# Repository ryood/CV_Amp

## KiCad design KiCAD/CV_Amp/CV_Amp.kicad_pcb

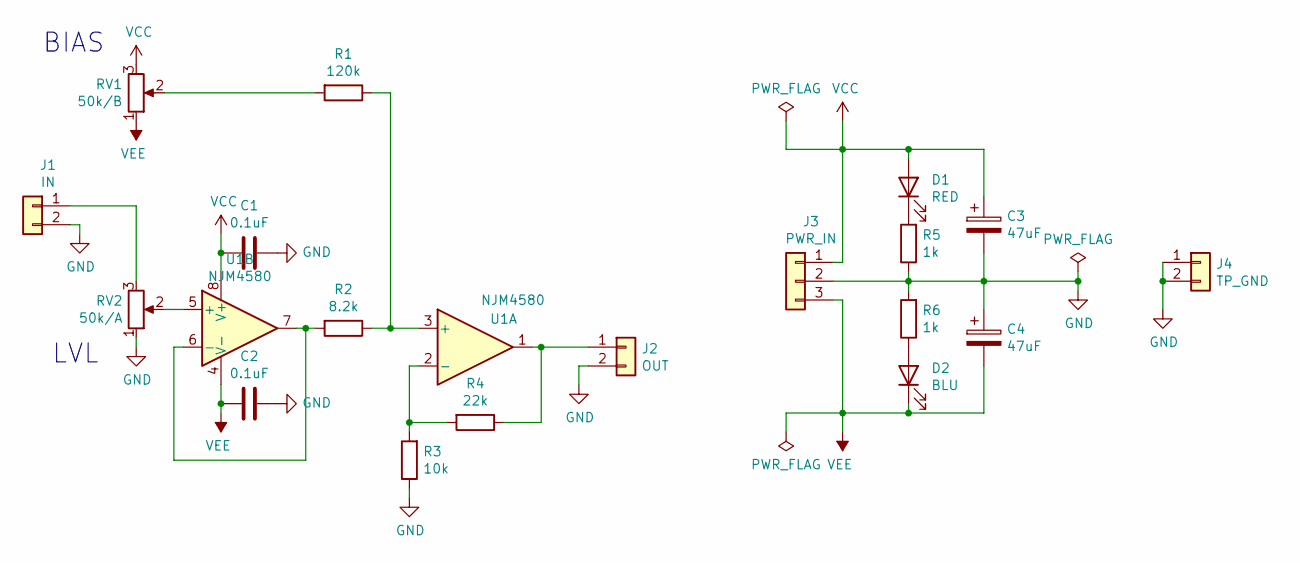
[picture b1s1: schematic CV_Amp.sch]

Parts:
C1, C2: 0.1uF; C_Disc_D3.0mm_W1.6mm_P2.50mm
C3, C4: 47uF; CP_Radial_D6.3mm_P2.50mm
D1: RED; LED_D3.0mm
D2: BLU; LED_D3.0mm
J1: IN; JST_XH_B2B-XH-A_1x02_P2.50mm_Vertical
J2: OUT; JST_XH_B2B-XH-A_1x02_P2.50mm_Vertical
J3: PWR_IN; JST_XH_B3B-XH-A_1x03_P2.50mm_Vertical
J4: TP_GND; PinHeader_1x02_P2.54mm_Vertical
R1: 120k; R_Axial_DIN0207_L6.3mm_D2.5mm_P7.62mm_Horizontal
R2: 8.2k; R_Axial_DIN0207_L6.3mm_D2.5mm_P7.62mm_Horizontal
R3: 10k; R_Axial_DIN0207_L6.3mm_D2.5mm_P7.62mm_Horizontal
R4: 22k; R_Axial_DIN0207_L6.3mm_D2.5mm_P7.62mm_Horizontal
R5, R6: 1k; R_Axial_DIN0207_L6.3mm_D2.5mm_P7.62mm_Horizontal
RV1: 50k/B; Potentiometer_Alps_RK097_Single_Horizontal
RV2: 50k/A; Potentiometer_Alps_RK097_Single_Horizontal
U1: NJM4580; DIP-8_W7.62mm_Socket

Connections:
GND: C1.1, C2.1, C3.2, C4.1, J1.2, J2.2, J3.2, J4.1, J4.2, R3.1, R5.1, R6.2, RV2.1
unnamed: D1.1 (K), R5.2
unnamed: D2.2 (A), R6.1
unnamed: J1.1, RV2.3
unnamed: J2.1, R4.1, U1.1
unnamed: R1.1, R2.1, U1.3 (+)
unnamed: R1.2, RV1.2
unnamed: R2.2, U1.6 (-), U1.7
unnamed: R3.2, R4.2, U1.2 (-)
unnamed: RV2.2, U1.5 (+)
VCC: C1.2, C3.1, D1.2 (A), J3.1, RV1.3, U1.8 (V+)
VEE: C2.2, C4.2, D2.1 (K), J3.3, RV1.1, U1.4 (V-)

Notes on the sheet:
BIAS
LVL

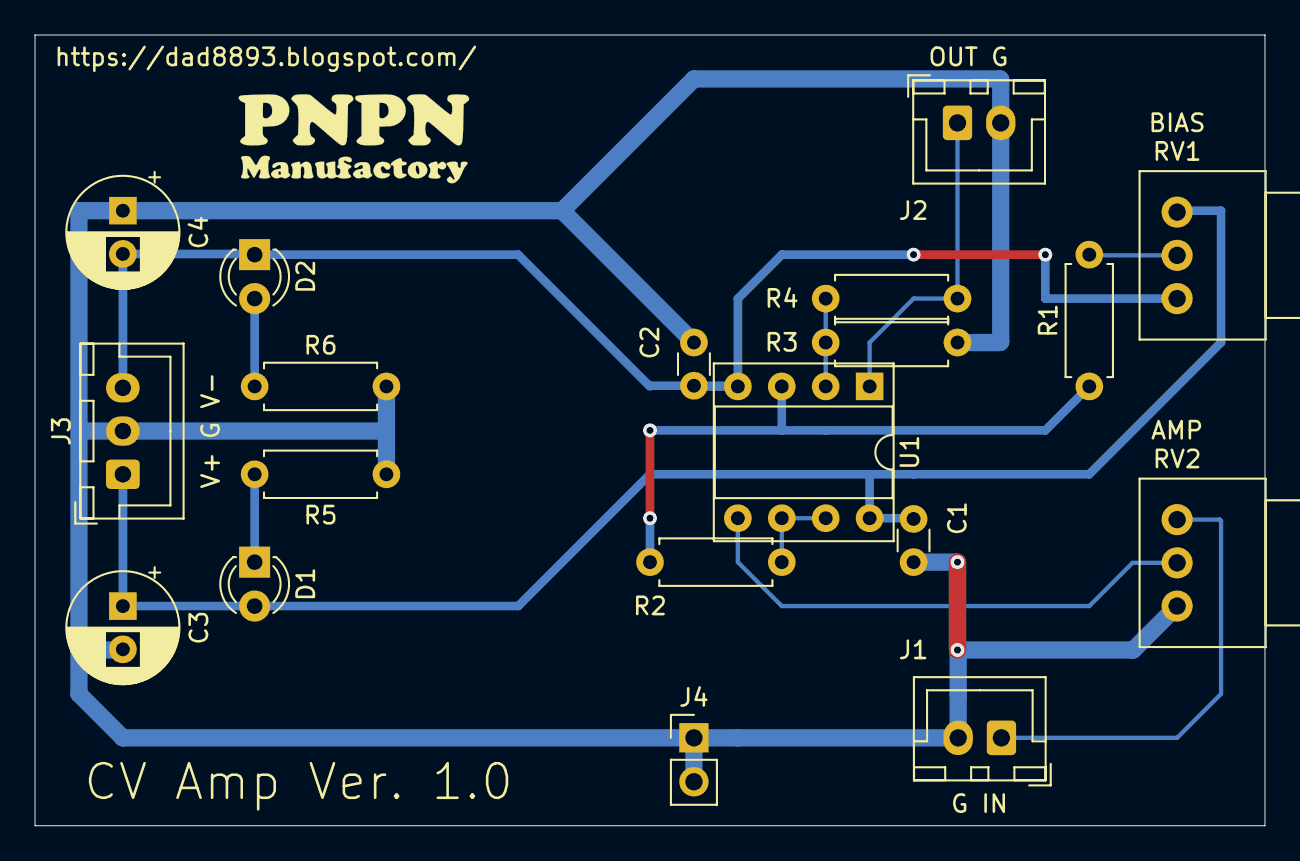
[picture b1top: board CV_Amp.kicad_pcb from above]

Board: 2 copper layers, 71.1 x 45.7 mm, 19 parts (0 on the bottom side), 12 nets.
